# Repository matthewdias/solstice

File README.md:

# solstice
 
40s mods drop-in pcb for equinox

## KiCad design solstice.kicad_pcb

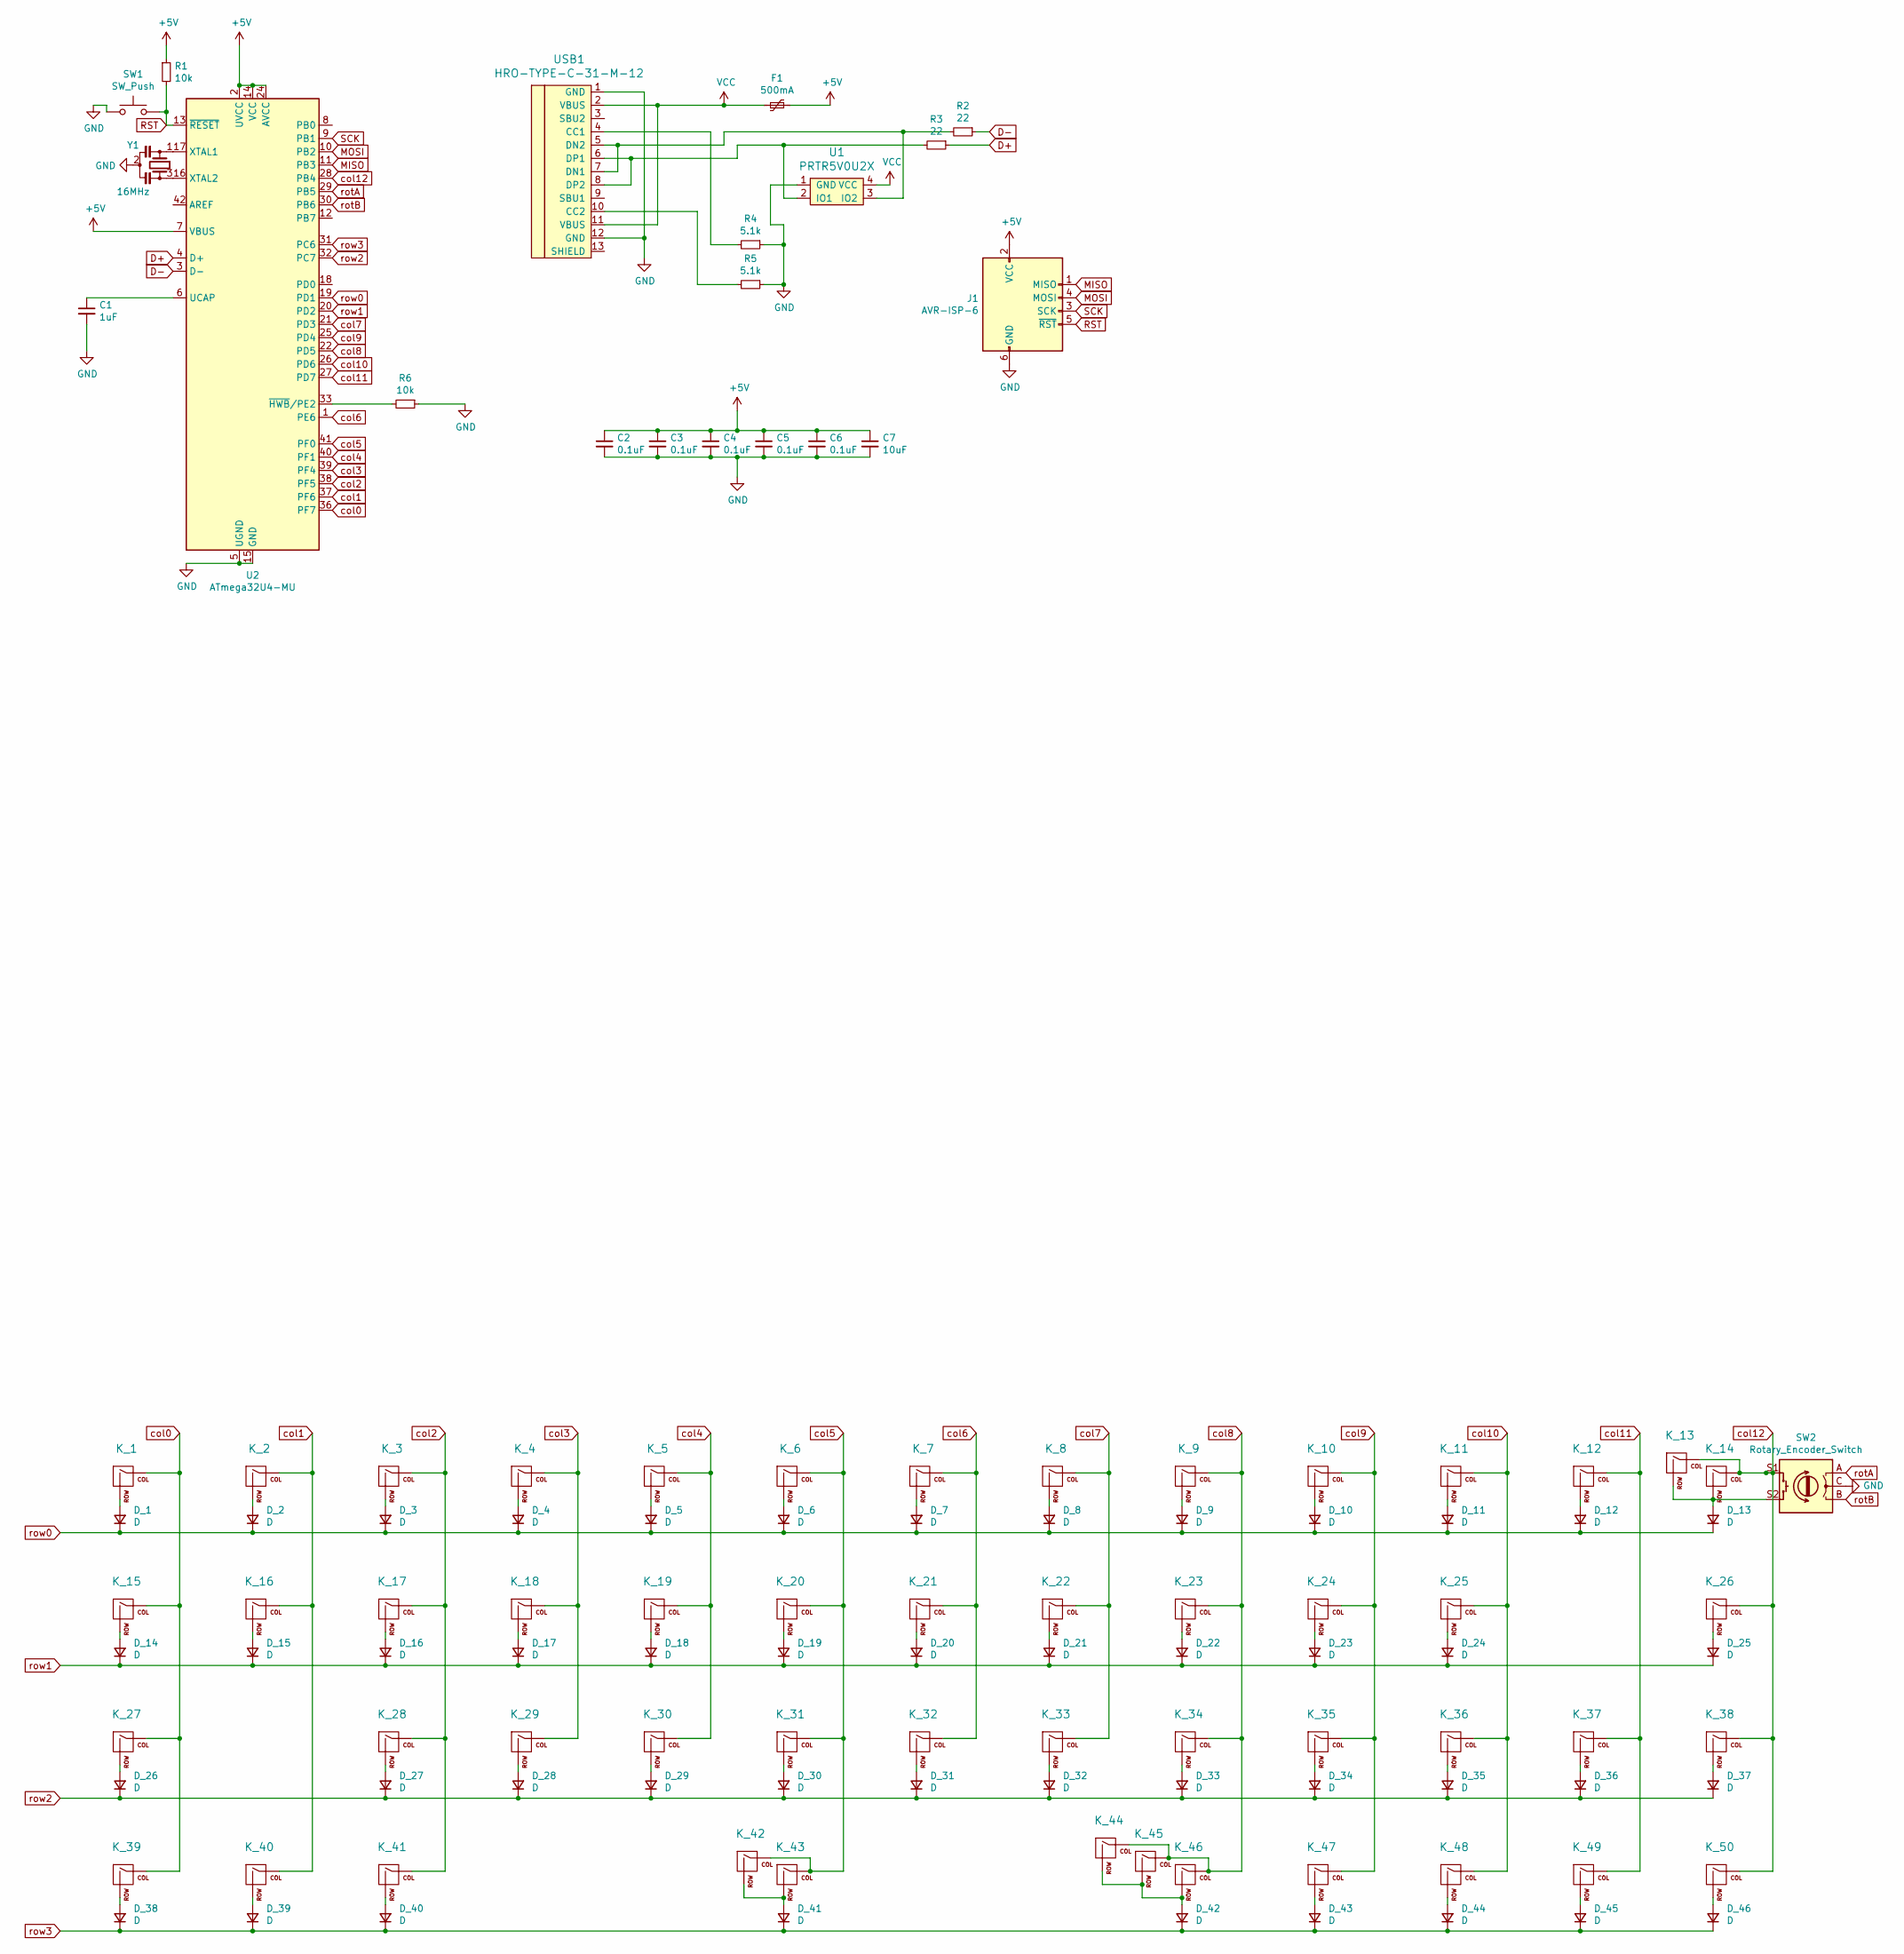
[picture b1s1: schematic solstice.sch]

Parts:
C1: 1uF; C_0603_1608Metric
C2, C3, C4, C5, C6: 0.1uF; C_0603_1608Metric
C7: 10uF; C_0603_1608Metric
D_1, D_2, D_3, D_4, D_5, D_6, D_7, D_8, D_9, D_10, D_11, D_12, D_13, D_14, D_15, D_16, D_17, D_18, D_19, D_20, D_21, D_22, D_23, D_24, D_25, D_26, D_27, D_28, D_29, D_30, D_31, D_32, D_33, D_34, D_35, D_36, D_37, D_38, D_39, D_40, D_41, D_42, D_43, D_44, D_45, D_46: D; D_SOD-123
F1: 500mA; Fuse_1206_3216Metric
J1: AVR-ISP-6; ISP-Staggered
K_1, K_2, K_3, K_4, K_5, K_6, K_7, K_8, K_9, K_10, K_11, K_12, K_14, K_16, K_17, K_18, K_19, K_20, K_21, K_22, K_23, K_24, K_25, K_28, K_29, K_30, K_31, K_32, K_33, K_34, K_35, K_36, K_37, K_40, K_47, K_49: KEYSW; MXOnly-1U-NoLED
K_13: KEYSW; MXOnly-2U-NoLED
K_15, K_38, K_39, K_41, K_48, K_50: KEYSW; MXOnly-1.25U-NoLED
K_26, K_27: KEYSW; MXOnly-1.75U-NoLED
K_42: KEYSW; MXOnly-2.75U-ReversedStabilizers-NoLED
K_43, K_46: KEYSW; MXOnly-3U-ReversedStabilizers-NoLED
K_44: KEYSW; MXOnly-6U-Centered-ReversedStabilizers-NoLED
K_45: KEYSW; MXOnly-2.25U-ReversedStabilizers-NoLED
R1, R6: 10k; R_0603_1608Metric
R2, R3: 22; R_0603_1608Metric
R4, R5: 5.1k; R_0603_1608Metric
SW1: SW_Push; SKQG-1155865
SW2: Rotary_Encoder_Switch; RotaryEncoder_Alps_EC11E-Switch_Vertical_H20mm_adjusted
U1: PRTR5V0U2X; SOT143B
U2: ATmega32U4-MU; QFN-44-1EP_7x7mm_P0.5mm_EP5.2x5.2mm
USB1: HRO-TYPE-C-31-M-12; HRO-TYPE-C-31-M-12-Assembly
Y1: 16MHz; Resonator_SMD_muRata_CSTxExxV-3Pin_3.0x1.1mm

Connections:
+5V: C2.1, C3.1, C4.1, C5.1, C6.1, C7.1, F1.1, J1.2 (VCC), R1.1, U2.2 (UVCC), U2.7 (VBUS), U2.14 (VCC), U2.24 (AVCC), U2.34 (VCC), U2.44 (AVCC)
D+: R3.1, U2.4 (D+)
D-: R2.1, U2.3 (D-)
GND: C1.2, C2.2, C3.2, C4.2, C5.2, C6.2, C7.2, J1.6 (GND), R4.1, R5.1, R6.1, SW1.1, SW2.C, U1.1 (GND), U2.5 (UGND), U2.15 (GND), U2.23 (GND), U2.35 (GND), U2.43 (GND), U2.45 (GND), USB1.1 (GND), USB1.12 (GND), Y1.2
MISO: J1.1 (MISO), U2.11 (PB3)
MOSI: J1.4 (MOSI), U2.10 (PB2)
unnamed: C1.1, U2.6 (UCAP)
unnamed: D_1.2 (A), K_1.2 (ROW)
unnamed: D_2.2 (A), K_2.2 (ROW)
unnamed: D_3.2 (A), K_3.2 (ROW)
unnamed: D_4.2 (A), K_4.2 (ROW)
unnamed: D_5.2 (A), K_5.2 (ROW)
unnamed: D_6.2 (A), K_6.2 (ROW)
unnamed: D_7.2 (A), K_7.2 (ROW)
unnamed: D_8.2 (A), K_8.2 (ROW)
unnamed: D_9.2 (A), K_9.2 (ROW)
unnamed: D_10.2 (A), K_10.2 (ROW)
unnamed: D_11.2 (A), K_11.2 (ROW)
unnamed: D_12.2 (A), K_12.2 (ROW)
unnamed: D_13.2 (A), K_13.2 (ROW), K_14.2 (ROW), SW2.S2
unnamed: D_14.2 (A), K_15.2 (ROW)
unnamed: D_15.2 (A), K_16.2 (ROW)
unnamed: D_16.2 (A), K_17.2 (ROW)
unnamed: D_17.2 (A), K_18.2 (ROW)
unnamed: D_18.2 (A), K_19.2 (ROW)
unnamed: D_19.2 (A), K_20.2 (ROW)
unnamed: D_20.2 (A), K_21.2 (ROW)
unnamed: D_21.2 (A), K_22.2 (ROW)
unnamed: D_22.2 (A), K_23.2 (ROW)
unnamed: D_23.2 (A), K_24.2 (ROW)
unnamed: D_24.2 (A), K_25.2 (ROW)
unnamed: D_25.2 (A), K_26.2 (ROW)
unnamed: D_26.2 (A), K_27.2 (ROW)
unnamed: D_27.2 (A), K_28.2 (ROW)
unnamed: D_28.2 (A), K_29.2 (ROW)
unnamed: D_29.2 (A), K_30.2 (ROW)
unnamed: D_30.2 (A), K_31.2 (ROW)
unnamed: D_31.2 (A), K_32.2 (ROW)
unnamed: D_32.2 (A), K_33.2 (ROW)
unnamed: D_33.2 (A), K_34.2 (ROW)
unnamed: D_34.2 (A), K_35.2 (ROW)
unnamed: D_35.2 (A), K_36.2 (ROW)
unnamed: D_36.2 (A), K_37.2 (ROW)
unnamed: D_37.2 (A), K_38.2 (ROW)
unnamed: D_38.2 (A), K_39.2 (ROW)
unnamed: D_39.2 (A), K_40.2 (ROW)
unnamed: D_40.2 (A), K_41.2 (ROW)
unnamed: D_41.2 (A), K_42.2 (ROW), K_43.2 (ROW)
unnamed: D_42.2 (A), K_44.2 (ROW), K_45.2 (ROW), K_46.2 (ROW)
unnamed: D_43.2 (A), K_47.2 (ROW)
unnamed: D_44.2 (A), K_48.2 (ROW)
unnamed: D_45.2 (A), K_49.2 (ROW)
unnamed: D_46.2 (A), K_50.2 (ROW)
unnamed: R2.2, U1.3 (IO2), USB1.5 (DN2), USB1.7 (DN1)
unnamed: R3.2, U1.2 (IO1), USB1.6 (DP1), USB1.8 (DP2)
unnamed: R4.2, USB1.4 (CC1)
unnamed: R5.2, USB1.10 (CC2)
unnamed: R6.2, U2.33 (~HWB~/PE2)
unnamed: U2.16 (XTAL2), Y1.3
unnamed: U2.17 (XTAL1), Y1.1
RST: J1.5 (~RST), R1.2, SW1.2, U2.13 (~RESET)
SCK: J1.3 (SCK), U2.9 (PB1)
VCC: F1.2, U1.4 (VCC), USB1.2 (VBUS), USB1.11 (VBUS)
col0: K_1.1 (COL), K_15.1 (COL), K_27.1 (COL), K_39.1 (COL), U2.36 (PF7)
col1: K_2.1 (COL), K_16.1 (COL), K_40.1 (COL), U2.37 (PF6)
col2: K_3.1 (COL), K_17.1 (COL), K_28.1 (COL), K_41.1 (COL), U2.38 (PF5)
col3: K_4.1 (COL), K_18.1 (COL), K_29.1 (COL), U2.39 (PF4)
col4: K_5.1 (COL), K_19.1 (COL), K_30.1 (COL), U2.40 (PF1)
col5: K_6.1 (COL), K_20.1 (COL), K_31.1 (COL), K_42.1 (COL), K_43.1 (COL), U2.41 (PF0)
col6: K_7.1 (COL), K_21.1 (COL), K_32.1 (COL), U2.1 (PE6)
col7: K_8.1 (COL), K_22.1 (COL), K_33.1 (COL), U2.21 (PD3)
col8: K_9.1 (COL), K_23.1 (COL), K_34.1 (COL), K_44.1 (COL), K_45.1 (COL), K_46.1 (COL), U2.22 (PD5)
col9: K_10.1 (COL), K_24.1 (COL), K_35.1 (COL), K_47.1 (COL), U2.25 (PD4)
col10: K_11.1 (COL), K_25.1 (COL), K_36.1 (COL), K_48.1 (COL), U2.26 (PD6)
col11: K_12.1 (COL), K_37.1 (COL), K_49.1 (COL), U2.27 (PD7)
col12: K_13.1 (COL), K_14.1 (COL), K_26.1 (COL), K_38.1 (COL), K_50.1 (COL), SW2.S1, U2.28 (PB4)
rotA: SW2.A, U2.29 (PB5)
rotB: SW2.B, U2.30 (PB6)
row0: D_1.1 (K), D_2.1 (K), D_3.1 (K), D_4.1 (K), D_5.1 (K), D_6.1 (K), D_7.1 (K), D_8.1 (K), D_9.1 (K), D_10.1 (K), D_11.1 (K), D_12.1 (K), D_13.1 (K), U2.19 (PD1)
row1: D_14.1 (K), D_15.1 (K), D_16.1 (K), D_17.1 (K), D_18.1 (K), D_19.1 (K), D_20.1 (K), D_21.1 (K), D_22.1 (K), D_23.1 (K), D_24.1 (K), D_25.1 (K), U2.20 (PD2)
row2: D_26.1 (K), D_27.1 (K), D_28.1 (K), D_29.1 (K), D_30.1 (K), D_31.1 (K), D_32.1 (K), D_33.1 (K), D_34.1 (K), D_35.1 (K), D_36.1 (K), D_37.1 (K), U2.32 (PC7)
row3: D_38.1 (K), D_39.1 (K), D_40.1 (K), D_41.1 (K), D_42.1 (K), D_43.1 (K), D_44.1 (K), D_45.1 (K), D_46.1 (K), U2.31 (PC6)

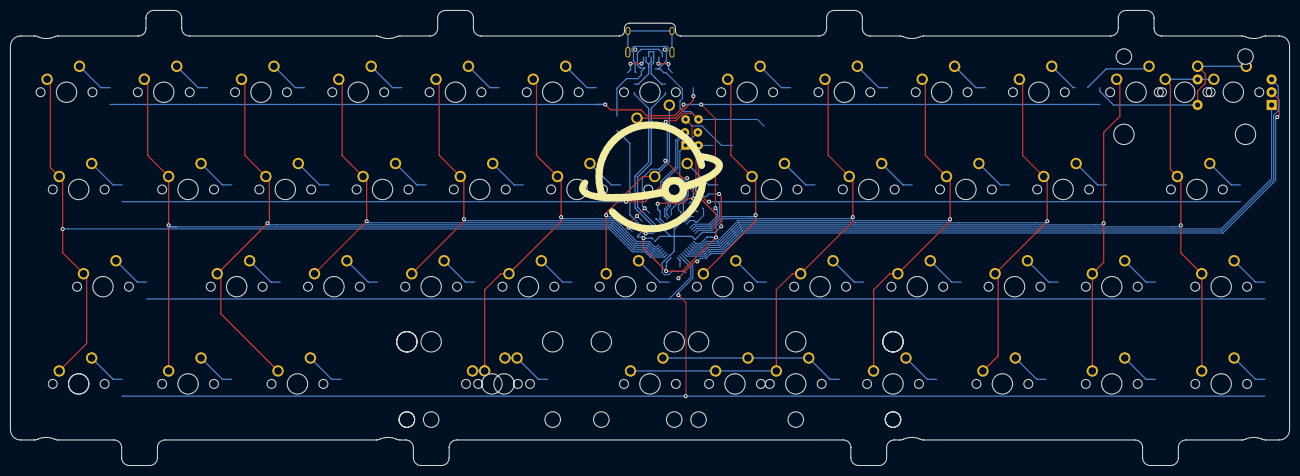
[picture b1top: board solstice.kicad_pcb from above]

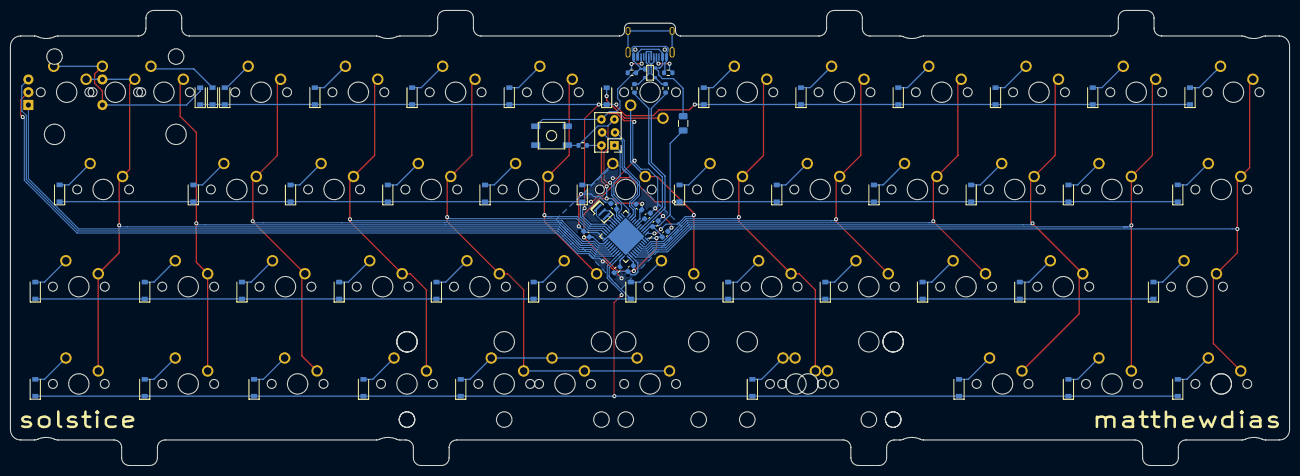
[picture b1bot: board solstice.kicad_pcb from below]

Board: 2 copper layers, 250.6 x 89.2 mm, 117 parts (66 on the bottom side), 82 nets.

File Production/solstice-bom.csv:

"Designator","Quantity",Value,Footprint,LCSC Part #
"C1, ","1",1uF,0603,C15849
"C2, C3, C4, C5, C6, ","5",0.1uF,0603,C14663
"C7, ","1",10uF,0603,C19702
"D_1, D_2, D_3, D_4, D_5, D_6, D_7, D_8, D_9, D_10, D_11, D_12, D_13, D_14, D_15, D_16, D_17, D_18, D_19, D_20, D_21, D_22, D_23, D_24, D_25, D_26, D_27, D_28, D_29, D_30, D_31, D_32, D_33, D_34, D_35, D_36, D_37, D_38, D_39, D_40, D_41, D_42, D_43, D_44, D_45, D_46, ","46",D,SOD-123,C64898
"F1, ","1",500mA,1206,C70076
"R1, R6, ","2",10k,0603,C25804
"R2, R3, ","2",22,0603,C23345
"R4, R5, ","2",5.1k,0603,C23186
"SW1, ","1",SW_Push,,C318884
"U1, ","1",PRTR5V0U2X,SOT143B,C316030
"U2, ","1",ATmega32U4-MU,QFN-44-1EP 7x7mm,C112161
"USB1, ","1",HRO-TYPE-C-31-M-12,,C165948
"Y1, ","1",16MHz,,C341521

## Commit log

2024-12-08 Unignore prod files
2024-12-08 Add images
